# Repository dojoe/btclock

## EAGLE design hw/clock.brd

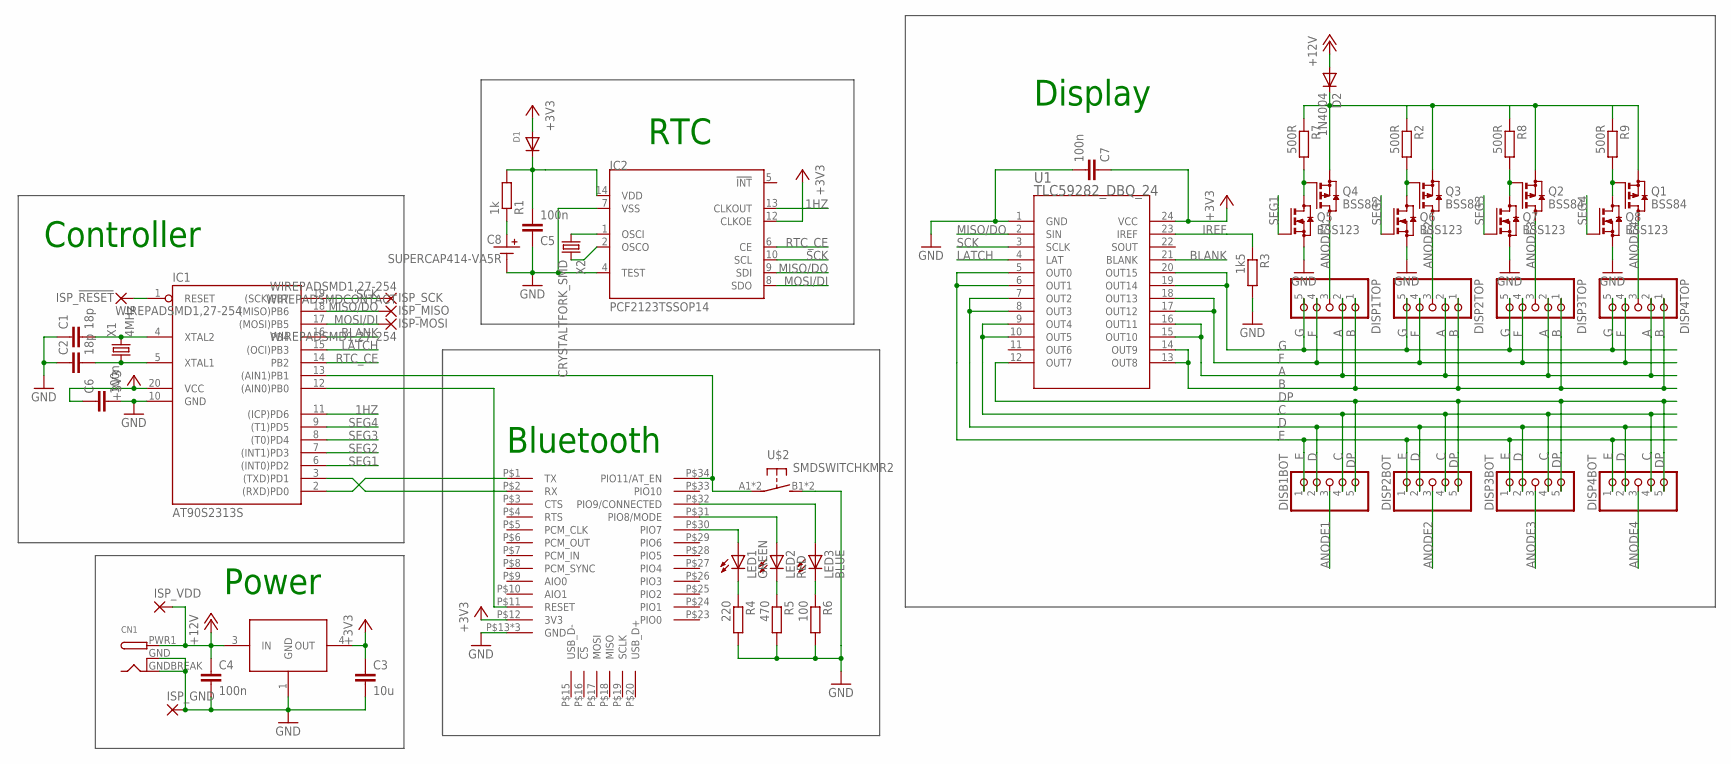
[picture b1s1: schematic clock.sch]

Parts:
C1, C2: 18p; C0603K
C3: 10u; C0805K
C4, C5, C6, C7: 100n; C0603K
C8: SUPERCAP414-VA5R; 414-VA5R
CN1: DCBARRELSMT; DCJACK_2MM_SMT
D1: DIODESOD-523; SOD-523
D2: 1N4004; DO41-10
DISB1BOT: PINHD-1X5; 1X05WIDE
DISP1TOP, DISP2BOT, DISP2TOP, DISP3BOT, DISP3TOP, DISP4BOT, DISP4TOP: PINHD-1X5; 1X05WIDE
IC1: AT90S2313S; SO20L
IC2: PCF2123TSSOP14; TSSOP14
ISP-MOSI: WIREPADSMD1,27-254; SMD1,27-2,54
ISP_!RESET: WIREPADSMD1,27-254; SMD1,27-2,54
ISP_GND: WIREPADSMD2,54-2,54; SMD2,54-2,54
ISP_MISO: WIREPADSMDCONTACT; SMDCONTACT
ISP_SCK: WIREPADSMD1,27-254; SMD1,27-2,54
ISP_VDD: WIREPADSMD2,54-2,54; SMD2,54-2,54
LED1: GREEN; CHIPLED_0805
LED2: RED; CHIPLED_0805
LED3: BLUE; CHIPLED_0805
Q1, Q2, Q3, Q4: BSS84; SOT23
Q5, Q6, Q7, Q8: BSS123; SOT23
R1: 1k; R0603
R2, R7, R8, R9: 500R; R0603
R3: 1k5; R0603
R4: 220; R0603
R5: 470; R0603
R6: 100; R0603
U1: TLC59282_DBQ_24; DBQ24
U$1: BT-HC-05
U$2: SMDSWITCHKMR2; KMR2
U$3: REGULATORDPAK; DPAK
X1: 4MHz; HC49UP
X2: CRYSTALTFORK_SMD; TFORK_SMD

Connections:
1HZ: IC1.11 ((ICP)PD6), IC2.13 (CLKOUT)
+3V3: C3.1, C6.1, C7.1, D1.A, IC1.20 (VCC), IC2.12 (CLKOE), U1.24 (VCC), U$1.P$12 (3V3), U$3.4 (OUT)
+12V: C4.1, CN1.PWR1 (PWR), D2.A, ISP_VDD.1, U$3.3 (IN)
A: DISP1TOP.2, DISP2TOP.2, DISP3TOP.2, DISP4TOP.2, U1.15 (OUT10), U1.16 (OUT11)
ANODE1: DISB1BOT.3, DISP1TOP.3, Q4.3 (D)
ANODE2: DISP2BOT.3, DISP2TOP.3, Q3.3 (D)
ANODE3: DISP3BOT.3, DISP3TOP.3, Q2.3 (D)
ANODE4: DISP4BOT.3, DISP4TOP.3, Q1.3 (D)
B: DISP1TOP.1, DISP2TOP.1, DISP3TOP.1, DISP4TOP.1, U1.13 (OUT8), U1.14 (OUT9)
BLANK: IC1.16 (PB4), U1.21 (BLANK)
C: DISB1BOT.4, DISP2BOT.4, DISP3BOT.4, DISP4BOT.4, U1.9 (OUT4), U1.10 (OUT5)
D: DISB1BOT.2, DISP2BOT.2, DISP3BOT.2, DISP4BOT.2, U1.7 (OUT2), U1.8 (OUT3)
DP: DISB1BOT.5, DISP2BOT.5, DISP3BOT.5, DISP4BOT.5, U1.12 (OUT7)
E: DISB1BOT.1, DISP2BOT.1, DISP3BOT.1, DISP4BOT.1, U1.5 (OUT0), U1.6 (OUT1)
F: DISP1TOP.4, DISP2TOP.4, DISP3TOP.4, DISP4TOP.4, U1.17 (OUT12), U1.18 (OUT13)
G: DISP1TOP.5, DISP2TOP.5, DISP3TOP.5, DISP4TOP.5, U1.19 (OUT14), U1.20 (OUT15)
GND: C1.1, C2.1, C3.2, C4.2, C5.1, C6.2, C7.2, C8.MINUS, CN1.GND (GNDBREAK), CN1.GNDBREAK (GND), IC1.10 (GND), IC2.4 (TEST), IC2.7 (VSS), ISP_GND.1, Q5.2 (S), Q6.2 (S), Q7.2 (S), Q8.2 (S), R3.2, R4.2, R5.2, R6.2, U1.1 (GND), U$1.P$13 (GND), U$1.P$21 (GND), U$1.P$22 (GND), U$2.B1 (S), U$2.B2 (S), U$3.1 (GND)
IREF: R3.1, U1.23 (IREF)
LATCH: IC1.15 ((OCI)PB3), U1.4 (LAT)
MISO/DO: IC1.18 ((MISO)PB6), IC2.9 (SDI), ISP_MISO.1, U1.2 (SIN)
MOSI/DI: IC1.17 ((MOSI)PB5), IC2.8 (SDO), ISP-MOSI.1
unnamed: IC1.2 ((RXD)PD0), U$1.P$1 (TX)
unnamed: IC1.3 ((TXD)PD1), U$1.P$2 (RX)
unnamed: IC2.2 (OSCO), X2.3 (2)
unnamed: IC2.1 (OSCI), X2.2 (1)
unnamed: C2.2, IC1.5 (XTAL1), X1.1
unnamed: C1.2, IC1.4 (XTAL2), X1.2
unnamed: IC1.1 (RESET), ISP_!RESET.1
unnamed: IC1.13 ((AIN1)PB1), U$1.P$34 (PIO11/AT_EN), U$2.A1, U$2.A2
unnamed: C8.PLUS, R1.1
unnamed: IC1.12 ((AIN0)PB0), U$1.P$11 (RESET)
unnamed: D2.C, Q1.2 (S), Q2.2 (S), Q3.2 (S), Q4.2 (S), R2.1, R7.1, R8.1, R9.1
unnamed: LED1.C, R4.1
unnamed: LED2.C, R5.1
unnamed: LED3.C, R6.1
unnamed: LED3.A, U$1.P$32 (PIO9/CONNECTED)
unnamed: LED2.A, U$1.P$31 (PIO8/MODE)
unnamed: LED1.A, U$1.P$30 (PIO7)
unnamed: Q1.1 (G), Q8.3 (D), R9.2
unnamed: Q2.1 (G), Q7.3 (D), R8.2
unnamed: Q3.1 (G), Q6.3 (D), R2.2
unnamed: Q4.1 (G), Q5.3 (D), R7.2
RTC_CE: IC1.14 (PB2), IC2.6 (CE)
SCK: IC1.19 ((SCK)PB7), IC2.10 (SCL), ISP_SCK.1, U1.3 (SCLK)
SEG1: IC1.6 ((INT0)PD2), Q5.1 (G)
SEG2: IC1.7 ((INT1)PD3), Q6.1 (G)
SEG3: IC1.8 ((T0)PD4), Q7.1 (G)
SEG4: IC1.9 ((T1)PD5), Q8.1 (G)
VRTC: C5.2, D1.K (C), IC2.14 (VDD), R1.2

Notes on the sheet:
Power
RTC
Controller
Bluetooth
Display

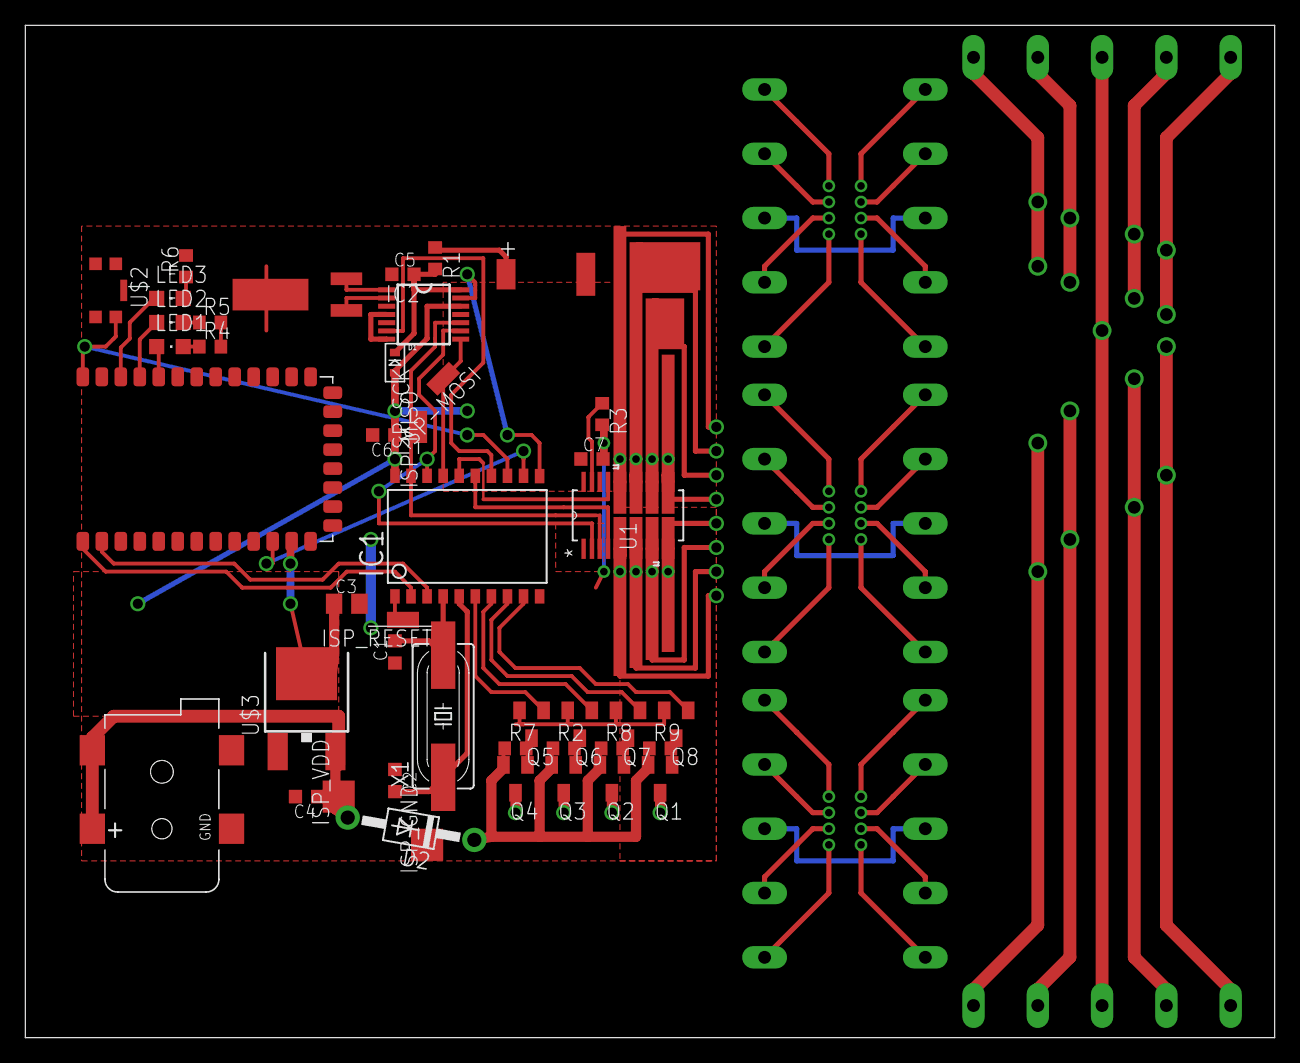
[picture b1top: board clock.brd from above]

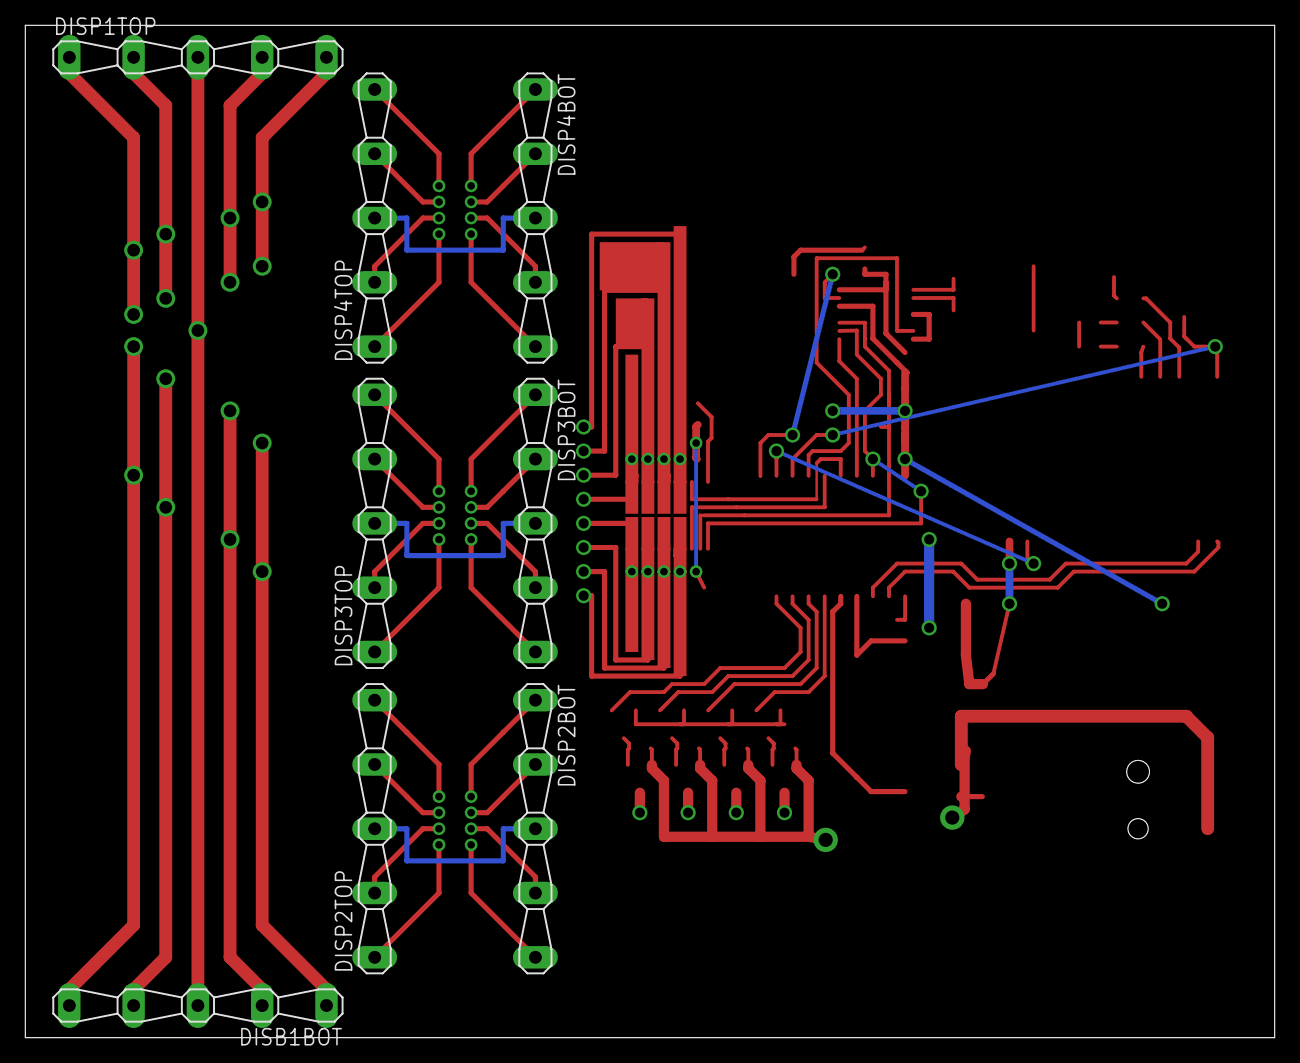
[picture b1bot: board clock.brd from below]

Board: 2 copper layers, 98.7 x 80.0 mm, 53 parts (8 on the bottom side), 49 nets.

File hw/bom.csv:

Qty;Value;Device;Package;Parts;Description;Digikey P/N;Vendor;Vendor P/N
1;;DCBARRELSMT;DCJACK_2MM_SMT;CN1;2.0mm DC Barrel Jack;CP-002AHPJCT-ND;CUI;PJ-002AH-SMT-TR
1;;DIODESOD-523;SOD-523;D1;Diode;DB2S20500LCT-ND;Panasonic;DB2S20500L
3;;LEDCHIPLED_0805;CHIPLED_0805;LED1, LED2, LED3;LED;div.;;
1;;R-EU_R0603;R0603;R1;RESISTOR, European symbol;;;
4;100n;C-EUC0603K;C0603K;C4, C5, C6, C7;CAPACITOR, European symbol;;;
1;10K;R-EU_R0603;R0603;R7;RESISTOR, European symbol;;;
1;10k;R-EU_R0603;R0603;R2;RESISTOR, European symbol;;;
1;10u;C-EUC0805K;C0805K;C3;CAPACITOR, European symbol;;;
2;18p;C-EUC0603K;C0603K;C1, C2;CAPACITOR, European symbol;;;
1;1k5;R-EU_R0603;R0603;R3;RESISTOR, European symbol;RMCF0603FT1K50CT-ND;;
3;470;R-EU_R0603;R0603;R4, R5, R6;RESISTOR, European symbol;;;
1;4MHz;CRYSTALHC49UP;HC49UP;X1;CRYSTAL;CTX879CT-ND;;
1;AT90S2313S;AT90S2313S;SO20L;IC1;MICROCONTROLLER;ATTINY4313-SURCT-ND;;
4;BSS84;BSS84;SOT23;Q1, Q2, Q3, Q4;P-CHANNEL MOS FET;;Taiwan Semiconductor;TSM2301CX
1;BT-HC-05;BT-HC-05;BT-HC-05;U$1;;;;
1;CRYSTALTFORK_SMD;CRYSTALTFORK_SMD;TFORK_SMD;X2;;300-8736-1-ND;Citizen;CMR200T-32.768KDZY-UT
1;PCF2123TSSOP14;PCF2123TSSOP14;TSSOP14;IC2;edit this description;568-4534-1-ND;NXP;PCF2123TS
1;REGULATORDPAK;REGULATORDPAK;DPAK;U$3;;497-1235-1-ND;STMicro;497-1235-1-ND
1;SMDSWITCHKMR2;SMDSWITCHKMR2;KMR2;U$2;;;;
1;SUPERCAP414-VA5R;SUPERCAP414-VA5R;414-VA5R;C8;;587-2158-1-ND;Taiyo Yuden;PAS414HR-VA5R
1;TLC59282_DBQ_24;TLC59282_DBQ_24;DBQ24;U1;;296-28098-1-ND;TI;TLC59282DBQR

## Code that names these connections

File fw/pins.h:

/*
 * pins.h
 *
 *  Created on: 27.01.2013
 *      Author: dojoe
 */

#ifndef PINS_H_
#define PINS_H_

#include <avr/io.h>

/*
 * PD0, PD1 - UART
 * PD2 - 1HZ input / INT0
 * PD3-PD6 - Display Enable
 * PB0 - BT Reset
 * PB1 - BT AT Enable / Button
 * PB2 - RTC CE
 * PB3 - LATCH / OC1A
 * PB4 - BLANK / OC1B
 * PB5..PB7 - SPI (TLC, RTC)
 */

#define BTRESETPORT PORTB
#define BTRESETDDR  DDRB
#define BTRESET     PB0

#define BTATPORT    PORTB
#define BTATDDR     DDRB
#define BTATENABLE  PB1

#define BUTTONPIN   PINB
#define BUTTON      BTATENABLE

#define SPISCK      PB7
#define SPIDO       PB6

#define RTCCEPORT   PORTB
#define RTCCEDDR    DDRB
#define RTCCE       PB2

#define SEGPORT     PORTD
#define SEGDDR      DDRD
#define SEGBASE     BOARD_SEGBASE
#define SEGMASK     (0xF << SEGBASE)

#define LATCHPORT   PORTB
#define LATCHDDR    DDRB
#define LATCH       PB3
#define BLANK       PB4

#define HZPIN       PIND
#define HZDDR       DDRD
#define HZBIT       BOARD_HZBIT

#define PORTB_INIT  (1 << BTRESET) | (1 << BLANK)
#define DDRB_INIT   (1 << BTRESET) | (1 << RTCCE) | \
					(1 << LATCH) | (1 << BLANK) | (1 << SPISCK) | (1 << SPIDO)

#define PORTD_INIT  (1 << HZBIT)
#define DDRD_INIT   SEGMASK

#endif /* PINS_H_ */

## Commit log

2013-01-31 Initial commit, including reverse SPI bug on PCB
2013-01-31 Fix reversed SPI lines, remove superfluous pull-up on RTC.CLKOUT, improve vias.
2013-01-31 Combine port init values
2013-01-31 Some small size optimizations
2013-02-06 Connect button to BT module's AT_ENABLE pin
2013-02-06 Kludge shared Button/BT_AT pin, get RTC working, enable TLC
2013-02-10 Add case layout
2013-02-13 Scrolltext, config in EEPROM, setup via BT
2013-02-15 Date mode, better scrolling, PIN setup. Also don't drink and code =/
2013-02-16 Started implementing dark time, but getting what looks like stack overruns...
2013-02-16 Reduce static RAM usage a bit, fixing stack overruns
2013-02-17 Blank times feature complete
2013-02-17 Shameless birthday reminder ;)
2013-02-17 Alternate scrolling mode
2013-02-19 Add README
2013-02-19 Modularize timespan handling in preparation for new feature
2013-02-21 Add special timespans
2013-02-21 Bugfixes
2013-02-22 Some more datasheets
2013-02-22 HW v2.0, with proper level shifters
2013-02-25 Proper fullstop support, size optimizations, some bugfixes
2013-02-25 Add notion of weekdays (and weekend), update README
2013-02-25 Make sure changing PIN also works during blank times
2013-02-26 Shrink UART code, print scroll mode with lines
2013-03-17 Add support for Board v2
2013-04-20 Add 'line 0' feature for intermittent stuff
2013-10-27 Print bad commands, ignore disconnect messages, save a few bytes somewhere else so we still fit into 4K =/
2014-04-06 Fix countdown running at double speed
